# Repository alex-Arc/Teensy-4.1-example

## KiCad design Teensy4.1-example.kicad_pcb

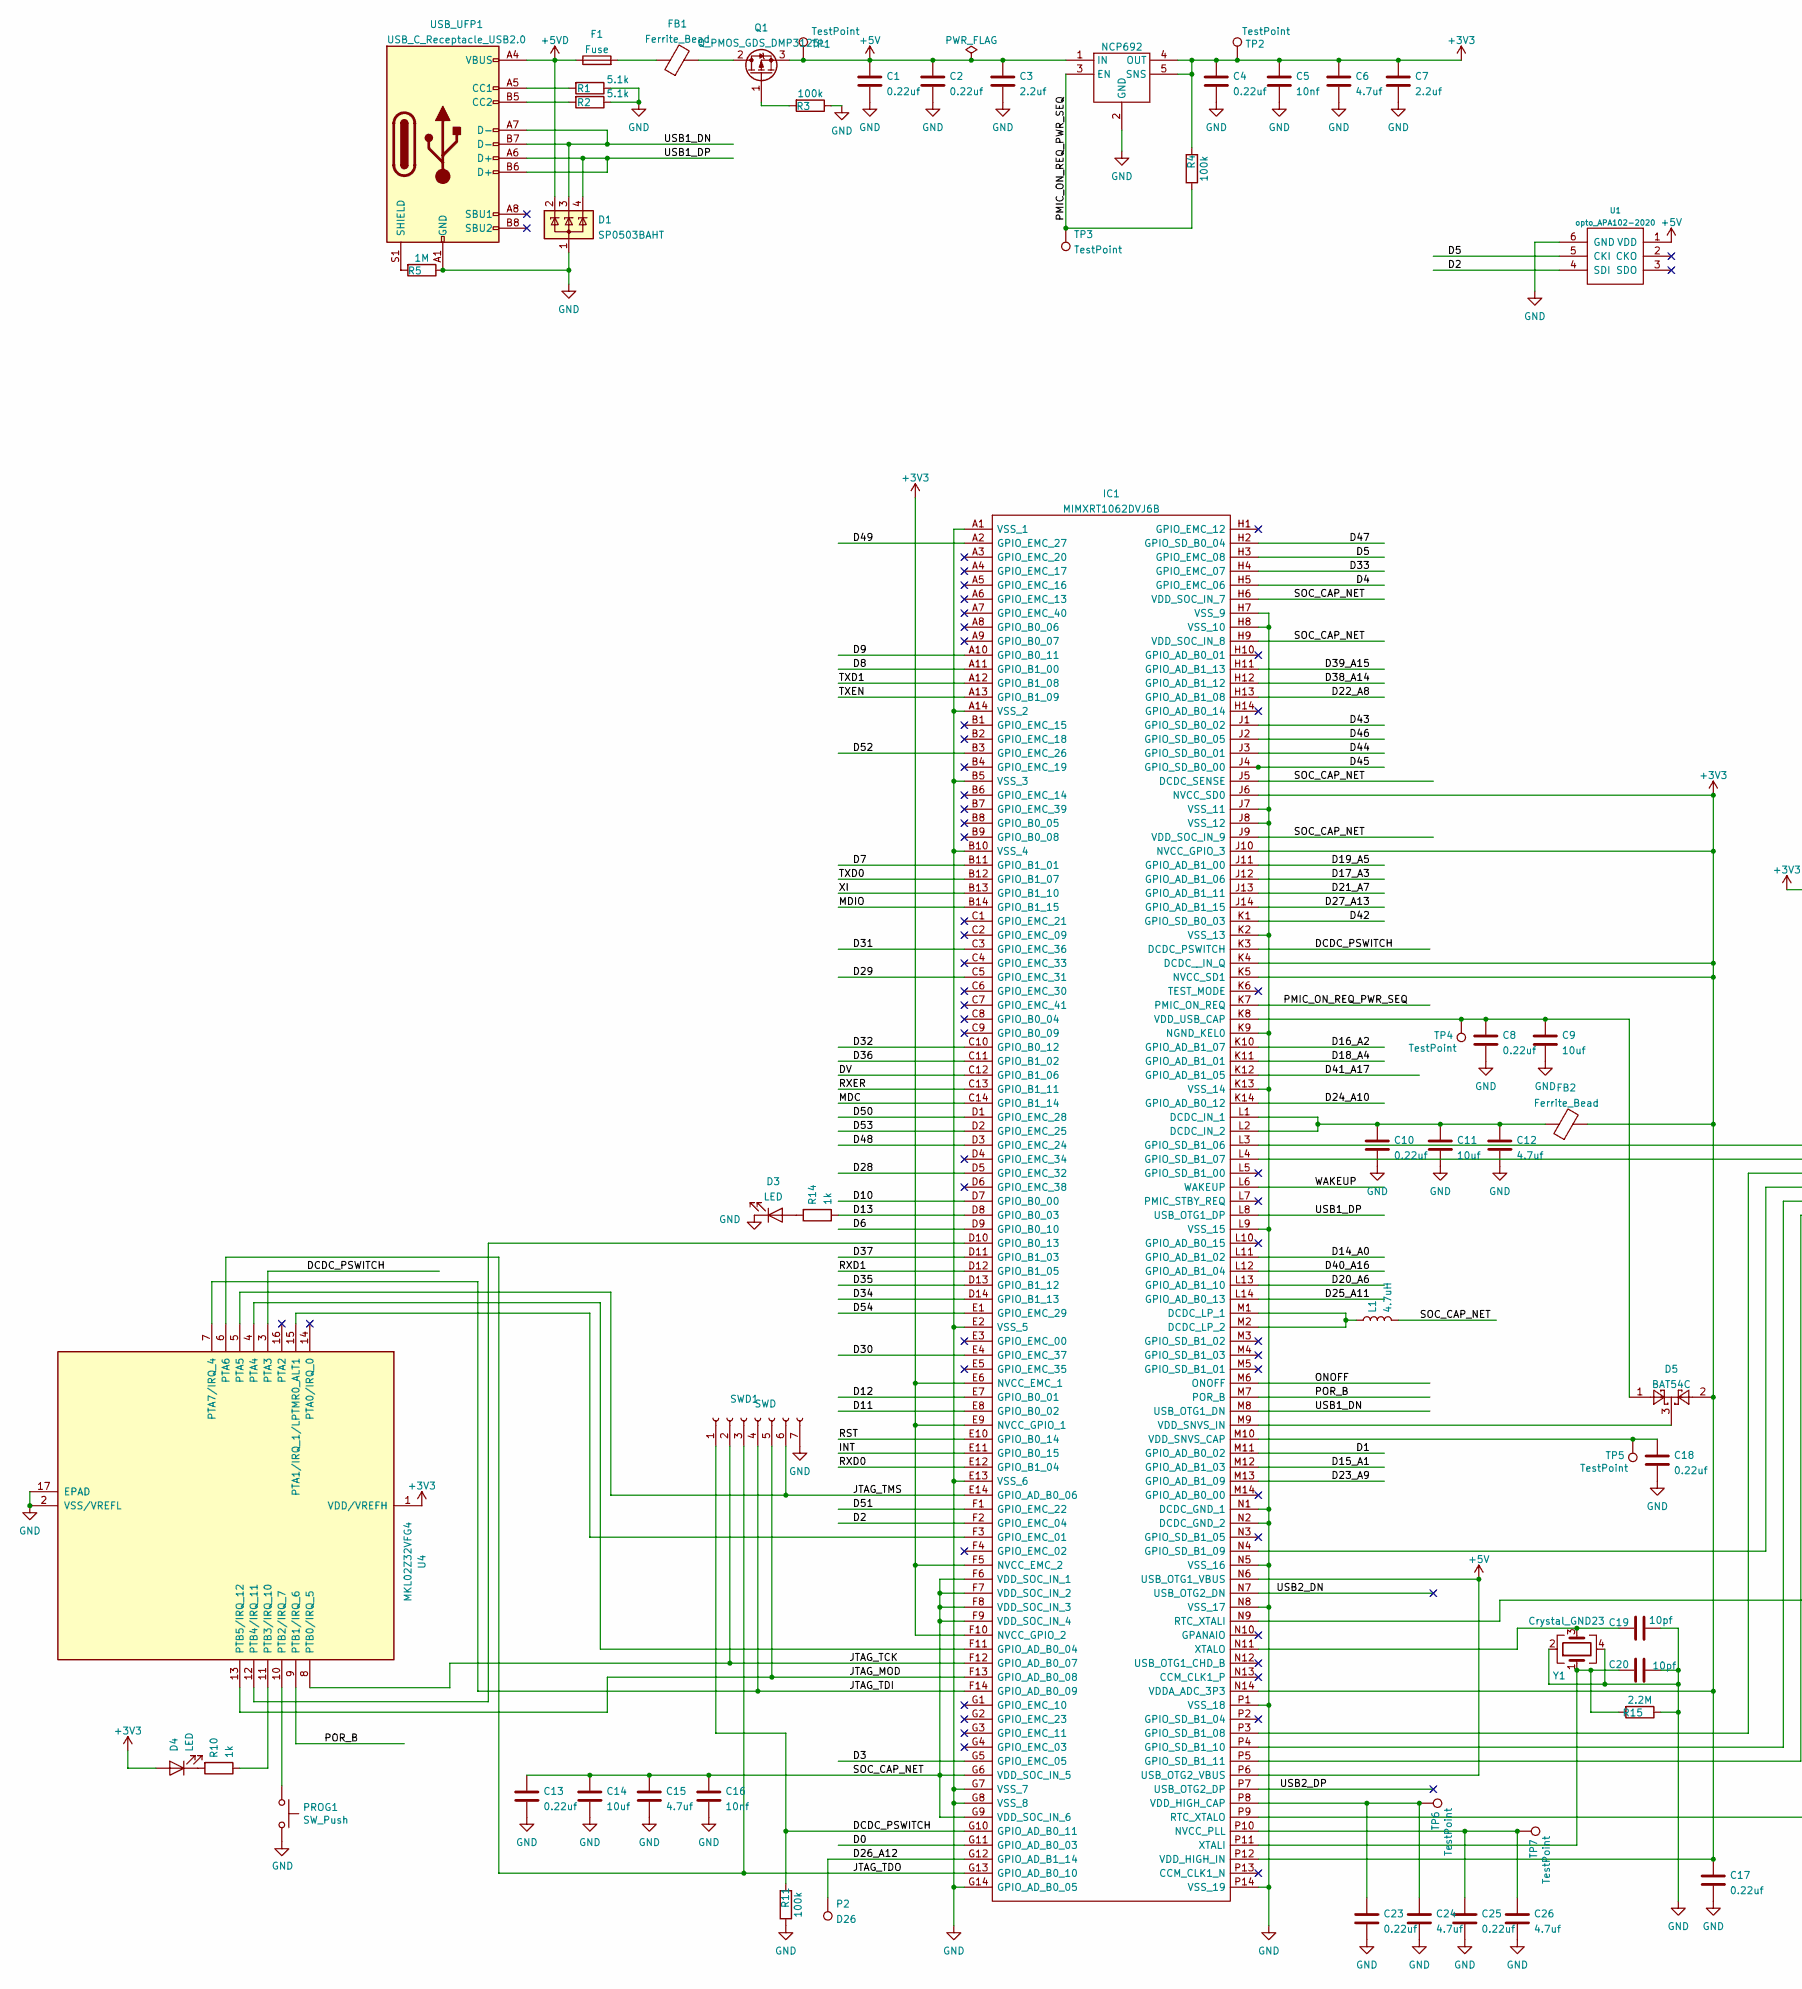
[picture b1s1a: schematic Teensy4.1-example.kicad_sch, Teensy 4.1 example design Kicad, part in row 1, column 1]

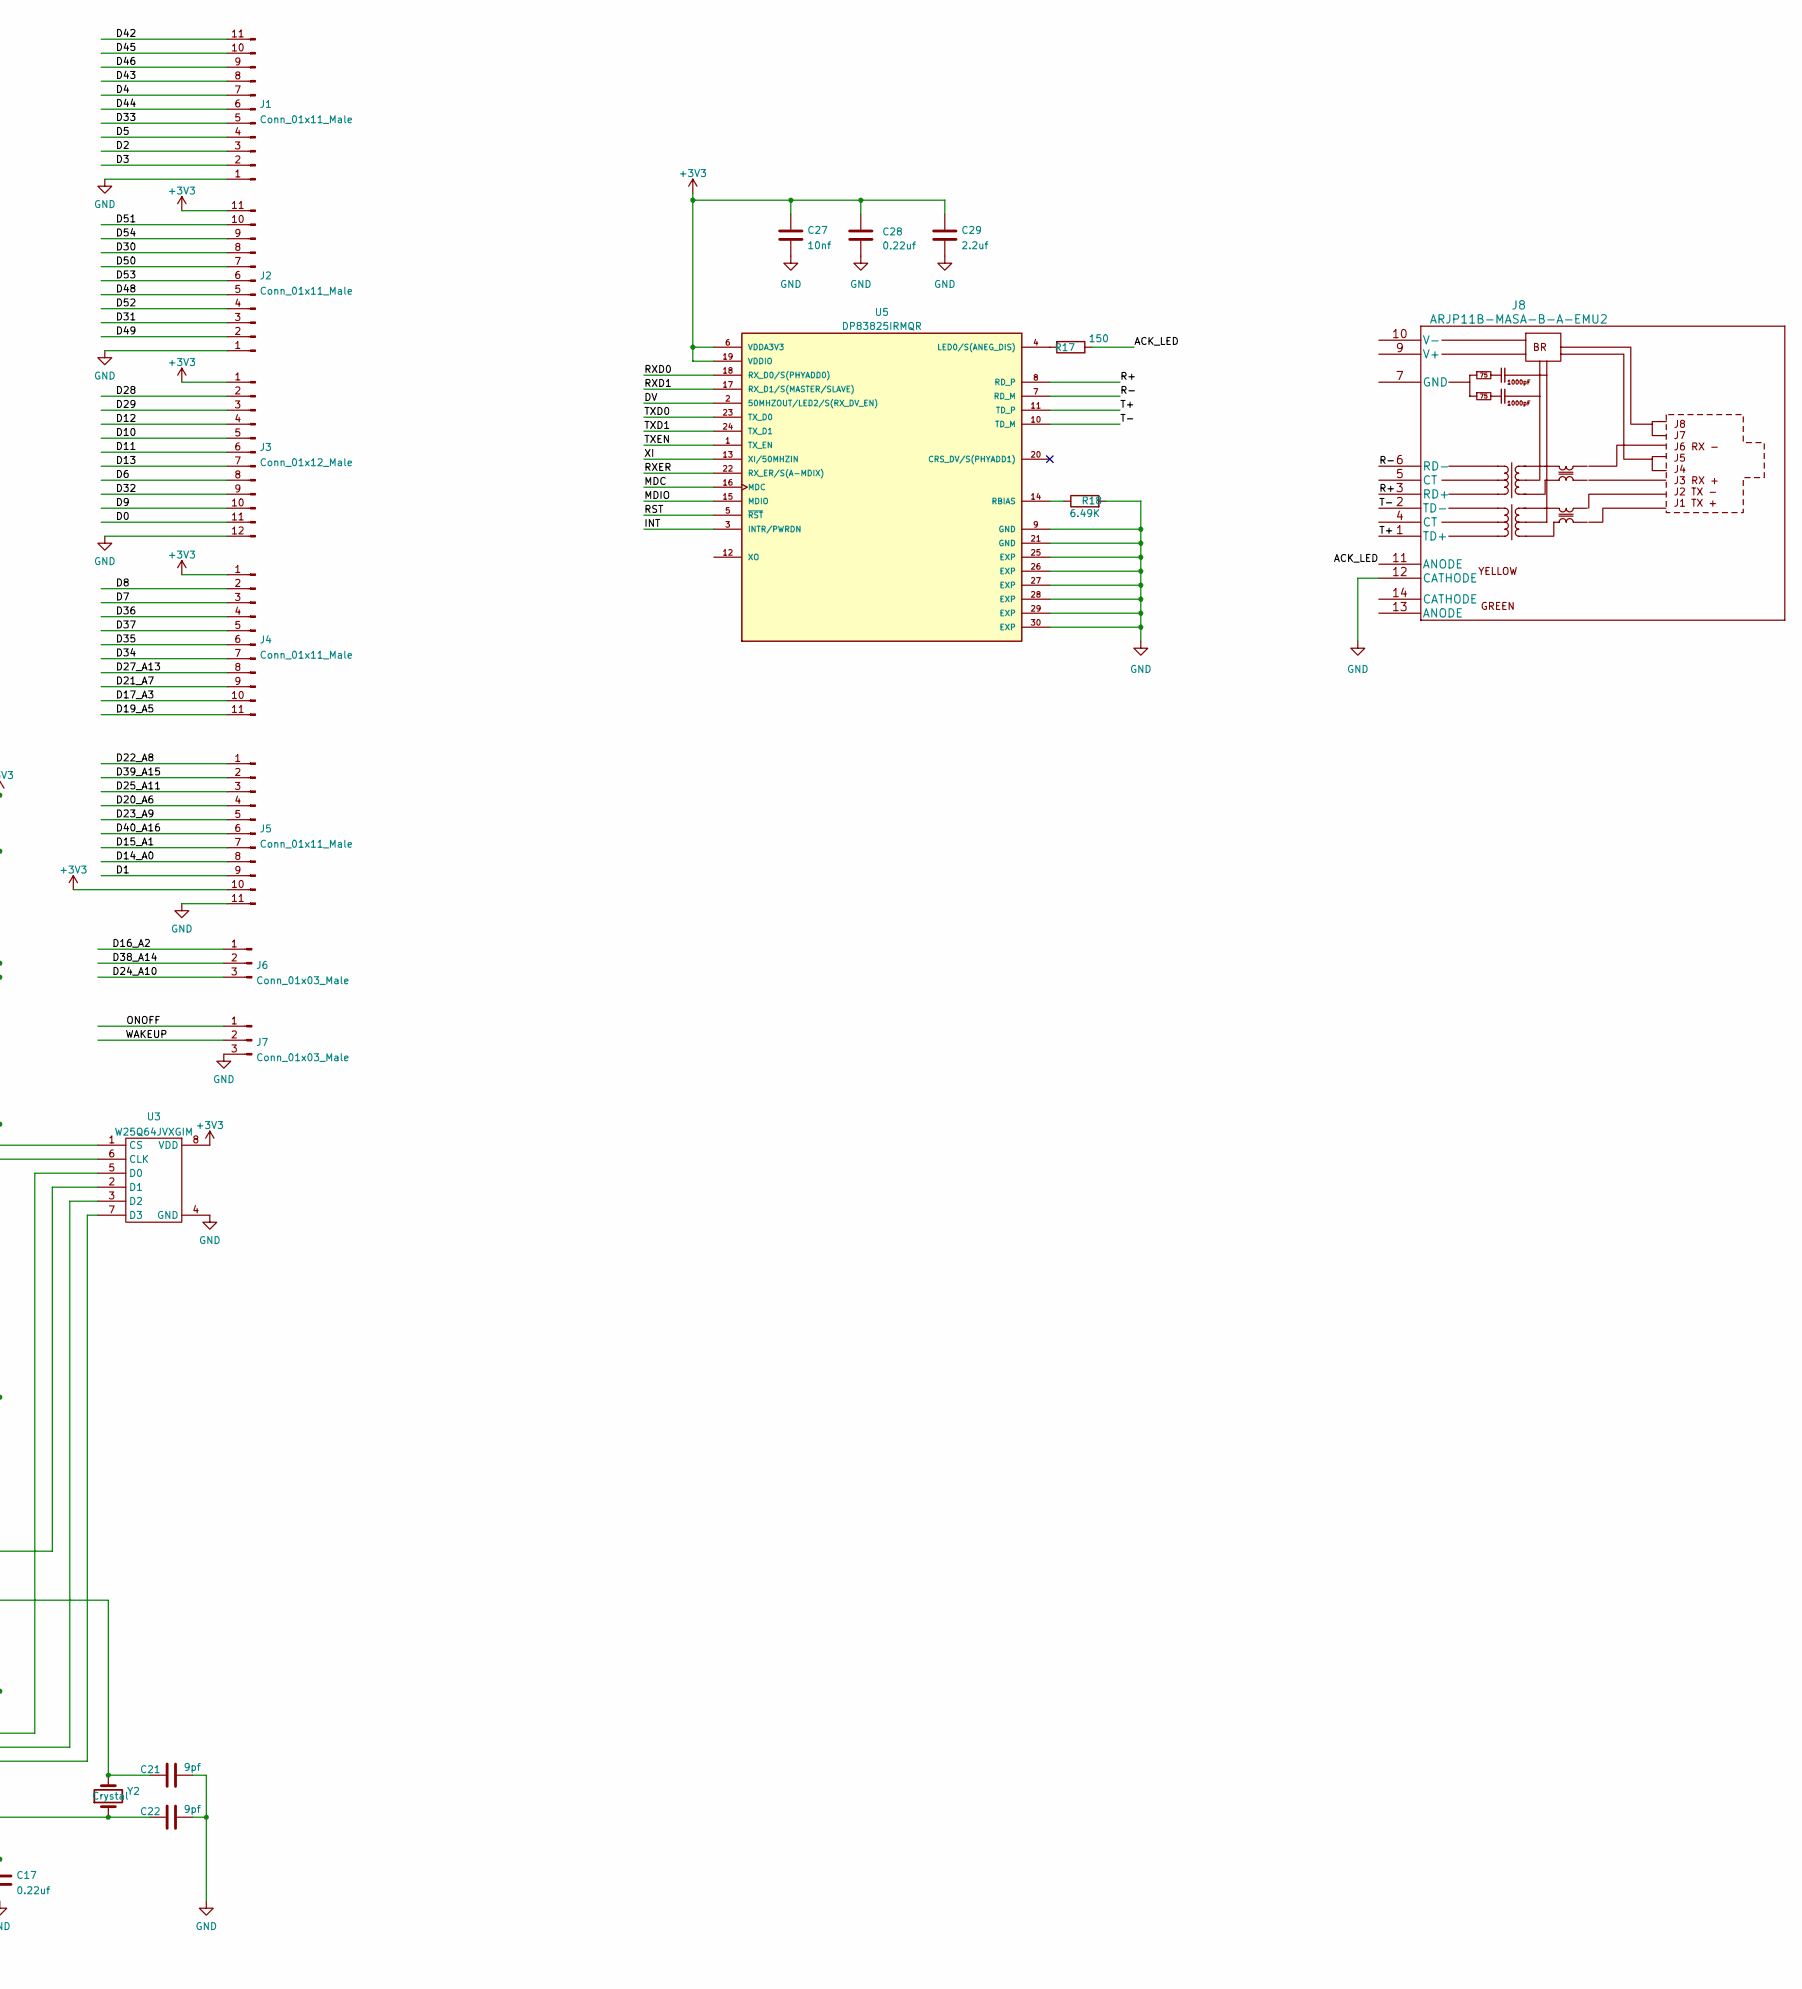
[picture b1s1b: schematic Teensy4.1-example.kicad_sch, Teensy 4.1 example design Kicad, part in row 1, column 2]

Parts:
C1, C2, C4, C8, C10, C13, C17, C18, C23, C25, C28: 0.22uf; C_0603_1608Metric; MPN CC0603KRX7R6BB224
C3, C7, C29: 2.2uf; C_0603_1608Metric; MPN CL10B225KP8NNNC
C5, C16, C27: 10nf; C_0603_1608Metric; MPN 0603B103K160CT
C6, C12, C15, C24, C26: 4.7uf; C_0603_1608Metric; MPN CL10B475KQ8NQNC
C9, C11, C14: 10uf; C_0805_2012Metric; MPN GRM21BR71A106KA73K
C19, C20: 10pf; C_0603_1608Metric; MPN CC0603KRX7R6BB224
C21, C22: 9pf; C_0603_1608Metric; MPN GRM1885C1H9R0DA01D
D1: SP0503BAHT; SOT-143
D3, D4: LED; LED_0402_1005Metric
D5: BAT54C; SOT-23
F1: Fuse; R_0805_2012Metric; MPN 0ZCK0050FF2E
FB1, FB2: Ferrite_Bead; R_0805_2012Metric; MPN FBMH2012HM121-T‎
IC1: MIMXRT1062DVJ6B; BGA196C80P14X14_1200X1200X152; Mouser Part Number 771-MIMXRT1062DVJ6B
J1, J2, J4, J5: Conn_01x11_Male; PinHeader_1x11_P2.54mm_Vertical
J3: Conn_01x12_Male; PinHeader_1x12_P2.54mm_Vertical
J6, J7: Conn_01x03_Male; PinHeader_1x03_P2.54mm_Vertical
J8: ARJP11B-MASA-B-A-EMU2
L1: 4.7uH; C_0805_2012Metric; MPN LQM21PN4R7MGRD
NCP692: OnSemi NCP692, fixed version; DFN-6-1EP_3x3mm_P0.95mm_EP1.7x2.6mm; MPN NCP692MN33T2G
P2: D26; PinHeader_1x01_P1.00mm_Vertical
PROG1: SW_Push; KMR241GLFS; MPN KMR241GLFS
Q1: Q_PMOS_GDS_DMP3125L; SOT-23
R1, R2: 5.1k; R_0603_1608Metric; MPN RC0603FR-075K1L
R3, R4, R11: 100k; R_0603_1608Metric
R5: 1M; R_0603_1608Metric
R10, R14: 1k; R_0402_1005Metric
R15: 2.2M; R_0603_1608Metric
R17: 150; R_0603_1608Metric; MPN RC0603FR-075K1L
R18: 6.49K; R_0603_1608Metric
SWD1: SWD; PinHeader_1x07_P1.27mm_Vertical
TP1, TP2, TP3, TP4, TP5, TP6, TP7: TestPoint; TestPoint_Pad_D1.0mm
U1: opto_APA102-2020; APA102-2020
U3: W25Q64JVXGIM; XSON8_4x4mm
U4: MKL02Z32VFG4; QFN-16-1EP_3x3mm_P0.5mm_EP1.8x1.8mm; MPN Custom firmware part
U5: DP83825IRMQR; XCVR_DP83825IRMQR; PARTREV A
USB_UFP1: USB_C_Receptacle_USB2.0; TYPE-C-31-M-14
Y1: Crystal_GND23; Crystal_SMD_Abracon_ABM3B-4Pin_5.0x3.2mm
Y2: Crystal; Crystal_SMD_2012-2Pin_2.0x1.2mm; MPN ABS06-32.768KHZ-9-1-T

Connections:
+3V3: C4.1, C5.1, C6.1, C7.1, C17.1, C27.1, C28.1, C29.1, D4.2 (A), D5.2, FB2.2, IC1.E6 (NVCC_EMC_1), IC1.E9 (NVCC_GPIO_1), IC1.F5 (NVCC_EMC_2), IC1.F10 (NVCC_GPIO_2), IC1.J6 (NVCC_SD0), IC1.J10 (NVCC_GPIO_3), IC1.K4 (DCDC__IN_Q), IC1.K5 (NVCC_SD1), IC1.N14 (VDDA_ADC_3P3), IC1.P12 (VDD_HIGH_IN), J2.11, J3.1, J4.1, J5.10, NCP692.4 (OUT), NCP692.5 (SNS), R4.2, TP2.1, U3.8 (VDD), U4.1 (VDD/VREFH), U5.6 (VDDA3V3), U5.19 (VDDIO)
+5V: C1.1, C2.1, C3.1, IC1.N6 (USB_OTG1_VBUS), IC1.P6 (USB_OTG2_VBUS), NCP692.1 (IN), NCP692.6 (IN), Q1.3 (S), TP1.1, U1.1 (VDD)
+5VD: D1.2 (K), F1.1, USB_UFP1.A4 (VBUS), USB_UFP1.A9 (VBUS), USB_UFP1.B4 (VBUS), USB_UFP1.B9 (VBUS); also elsewhere on the board
/ACK_LED: J8.11 (ANODE), R17.1
/D0: IC1.G11 (GPIO_AD_B0_03), J3.11
/D1: IC1.M11 (GPIO_AD_B0_02), J5.9
/D2: IC1.F2 (GPIO_EMC_04), J1.3, U1.4 (SDI)
/D3: IC1.G5 (GPIO_EMC_05), J1.2
/D4: IC1.H5 (GPIO_EMC_06), J1.7
/D5: IC1.H3 (GPIO_EMC_08), J1.4, U1.5 (CKI)
/D6: IC1.D9 (GPIO_B0_10), J3.8
/D7: IC1.B11 (GPIO_B1_01), J4.3
/D8: IC1.A11 (GPIO_B1_00), J4.2
/D9: IC1.A10 (GPIO_B0_11), J3.10
/D10: IC1.D7 (GPIO_B0_00), J3.5
/D11: IC1.E8 (GPIO_B0_02), J3.6
/D12: IC1.E7 (GPIO_B0_01), J3.4
/D13: IC1.D8 (GPIO_B0_03), J3.7, R14.1
/D14_A0: IC1.L11 (GPIO_AD_B1_02), J5.8
/D15_A1: IC1.M12 (GPIO_AD_B1_03), J5.7
/D16_A2: IC1.K10 (GPIO_AD_B1_07), J6.1
/D17_A3: IC1.J12 (GPIO_AD_B1_06), J4.10
/D18_A4: IC1.K11 (GPIO_AD_B1_01)
/D19_A5: IC1.J11 (GPIO_AD_B1_00), J4.11
/D20_A6: IC1.L13 (GPIO_AD_B1_10), J5.4
/D21_A7: IC1.J13 (GPIO_AD_B1_11), J4.9
/D22_A8: IC1.H13 (GPIO_AD_B1_08), J5.1
/D23_A9: IC1.M13 (GPIO_AD_B1_09), J5.5
/D24_A10: IC1.K14 (GPIO_AD_B0_12), J6.3
/D25_A11: IC1.L14 (GPIO_AD_B0_13), J5.3
/D26_A12: IC1.G12 (GPIO_AD_B1_14), P2.1
/D27_A13: IC1.J14 (GPIO_AD_B1_15), J4.8
/D28: IC1.D5 (GPIO_EMC_32), J3.2
/D29: IC1.C5 (GPIO_EMC_31), J3.3
/D30: IC1.E4 (GPIO_EMC_37), J2.8
/D31: IC1.C3 (GPIO_EMC_36), J2.3
/D32: IC1.C10 (GPIO_B0_12), J3.9
/D33: IC1.H4 (GPIO_EMC_07), J1.5
/D34: IC1.D14 (GPIO_B1_13), J4.7
/D35: IC1.D13 (GPIO_B1_12), J4.6
/D36: IC1.C11 (GPIO_B1_02), J4.4
/D37: IC1.D11 (GPIO_B1_03), J4.5
/D38_A14: IC1.H12 (GPIO_AD_B1_12), J6.2
/D39_A15: IC1.H11 (GPIO_AD_B1_13), J5.2
/D40_A16: IC1.L12 (GPIO_AD_B1_04), J5.6
/D41_A17: IC1.K12 (GPIO_AD_B1_05)
/D42: IC1.K1 (GPIO_SD_B0_03), J1.11
/D43: IC1.J1 (GPIO_SD_B0_02), J1.8
/D44: IC1.J3 (GPIO_SD_B0_01), J1.6
/D45: IC1.J4 (GPIO_SD_B0_00), J1.10
/D46: IC1.J2 (GPIO_SD_B0_05), J1.9
/D47: IC1.H2 (GPIO_SD_B0_04)
/D48: IC1.D3 (GPIO_EMC_24), J2.5
/D49: IC1.A2 (GPIO_EMC_27), J2.2
/D50: IC1.D1 (GPIO_EMC_28), J2.7
/D51: IC1.F1 (GPIO_EMC_22), J2.10
/D52: IC1.B3 (GPIO_EMC_26), J2.4
/D53: IC1.D2 (GPIO_EMC_25), J2.6
/D54: IC1.E1 (GPIO_EMC_29), J2.9
/DCDC_PSWITCH: IC1.G10 (GPIO_AD_B0_11), IC1.K3 (DCDC_PSWITCH), R11.2, SWD1.1, U4.3 (PTA3)
/DV: IC1.C12 (GPIO_B1_06), U5.2 (50MHZOUT/LED2/S(RX_DV_EN))
/INT: IC1.E11 (GPIO_B0_15), U5.3 (INTR/PWRDN)
/JTAG_MOD: IC1.F13 (GPIO_AD_B0_08), SWD1.5, U4.13 (PTB5/IRQ_12)
/JTAG_TCK: IC1.F12 (GPIO_AD_B0_07), SWD1.2, U4.8 (PTB0/IRQ_5)
/JTAG_TDI: IC1.F14 (GPIO_AD_B0_09), SWD1.4, U4.7 (PTA7/IRQ_4)
/JTAG_TDO: IC1.G13 (GPIO_AD_B0_10), SWD1.3, U4.6 (PTA6)
/JTAG_TMS: IC1.E14 (GPIO_AD_B0_06), SWD1.6, U4.5 (PTA5)
/MDC: IC1.C14 (GPIO_B1_14), U5.16 (MDC)
/MDIO: IC1.B14 (GPIO_B1_15), U5.15 (MDIO)
/ONOFF: IC1.M6 (ONOFF), J7.1
/PMIC_ON_REQ_PWR_SEQ: IC1.K7 (PMIC_ON_REQ), NCP692.3 (EN), R4.1, TP3.1
/POR_B: IC1.M7 (POR_B), U4.9 (PTB1/IRQ_6)
/R+: J8.3 (RD+), U5.8 (RD_P)
/R-: J8.6 (RD-), U5.7 (RD_M)
/RST: IC1.E10 (GPIO_B0_14), U5.5 (~RST)
/RXD0: IC1.E12 (GPIO_B1_04), U5.18 (RX_D0/S(PHYADD0))
/RXD1: IC1.D12 (GPIO_B1_05), U5.17 (RX_D1/S(MASTER/SLAVE))
/RXER: IC1.C13 (GPIO_B1_11), U5.22 (RX_ER/S(A-MDIX))
/SOC_CAP_NET: C13.1, C14.1, C15.1, C16.1, IC1.F6 (VDD_SOC_IN_1), IC1.F7 (VDD_SOC_IN_2), IC1.F8 (VDD_SOC_IN_3), IC1.F9 (VDD_SOC_IN_4), IC1.G6 (VDD_SOC_IN_5), IC1.G9 (VDD_SOC_IN_6), IC1.H6 (VDD_SOC_IN_7), IC1.H9 (VDD_SOC_IN_8), IC1.J5 (DCDC_SENSE), IC1.J9 (VDD_SOC_IN_9), L1.2
/T+: J8.1 (TD+), U5.11 (TD_P)
/T-: J8.2 (TD-), U5.10 (TD_M)
/TXD0: IC1.B12 (GPIO_B1_07), U5.23 (TX_D0)
/TXD1: IC1.A12 (GPIO_B1_08), U5.24 (TX_D1)
/TXEN: IC1.A13 (GPIO_B1_09), U5.1 (TX_EN)
/USB1_DN: D1.3 (K), IC1.M8 (USB_OTG1_DN), USB_UFP1.A7 (D-), USB_UFP1.B7 (D-)
/USB1_DP: D1.4 (K), IC1.L8 (USB_OTG1_DP), USB_UFP1.A6 (D+), USB_UFP1.B6 (D+)
/USB2_DN: IC1.N7 (USB_OTG2_DN)
/USB2_DP: IC1.P7 (USB_OTG2_DP)
/WAKEUP: IC1.L6 (WAKEUP), J7.2
/XI: IC1.B13 (GPIO_B1_10), U5.13 (XI/50MHZIN)
GND: C1.2, C2.2, C3.2, C4.2, C5.2, C6.2, C7.2, C8.2, C9.2, C10.2, C11.2, C12.2, C13.2, C14.2, C15.2, C16.2, C17.2, C18.2, C19.2, C20.2, C21.2, C22.2, C23.2, C24.2, C25.2, C26.2, C27.2, C28.2, C29.2, D1.1 (A), D3.1 (K), IC1.A1 (VSS_1), IC1.A14 (VSS_2), IC1.B5 (VSS_3), IC1.B10 (VSS_4), IC1.E2 (VSS_5), IC1.E13 (VSS_6), IC1.G7 (VSS_7), IC1.G8 (VSS_8), IC1.G14 (GPIO_AD_B0_05), IC1.H7 (VSS_9), IC1.H8 (VSS_10), IC1.J7 (VSS_11), IC1.J8 (VSS_12), IC1.K2 (VSS_13), IC1.K9 (NGND_KEL0), IC1.K13 (VSS_14), IC1.L9 (VSS_15), IC1.N1 (DCDC_GND_1), IC1.N2 (DCDC_GND_2), IC1.N5 (VSS_16), IC1.N8 (VSS_17), IC1.P1 (VSS_18), IC1.P14 (VSS_19), J1.1, J2.1, J3.12, J5.11, J7.3, J8.12 (CATHODE), NCP692.2 (GND), NCP692.7 (GND), PROG1.2, R1.1, R2.1, R3.1, R5.1, R11.1, R15.1, R18.2, SWD1.7, U1.6 (GND), U3.4 (GND), U4.2 (VSS/VREFL), U4.17 (EPAD), U5.9 (GND), U5.21 (GND), U5.25 (EXP), U5.26 (EXP), U5.27 (EXP), U5.28 (EXP), U5.29 (EXP), U5.30 (EXP), USB_UFP1.A1 (GND), USB_UFP1.A12 (GND), USB_UFP1.B1 (GND), USB_UFP1.B12 (GND), Y1.2, Y1.4; also elsewhere on the board
unnamed: D3.2 (A), R14.2
unnamed: D4.1 (K), R10.2
unnamed: F1.2, FB1.1
unnamed: C10.1, C11.1, C12.1, FB2.1, IC1.L1 (DCDC_IN_1), IC1.L2 (DCDC_IN_2)
unnamed: IC1.M1 (DCDC_LP_1), IC1.M2 (DCDC_LP_2), L1.1
unnamed: IC1.F11 (GPIO_AD_B0_04), U4.4 (PTA4)
unnamed: IC1.D10 (GPIO_B0_13), U4.12 (PTB4/IRQ_11)
unnamed: IC1.F3 (GPIO_EMC_01), U4.15 (PTA1/IRQ_1/LPTMR0_ALT1)
unnamed: IC1.L3 (GPIO_SD_B1_06), U3.1 (CS)
unnamed: IC1.L4 (GPIO_SD_B1_07), U3.6 (CLK)
unnamed: IC1.P3 (GPIO_SD_B1_08), U3.5 (D0)
unnamed: IC1.N4 (GPIO_SD_B1_09), U3.2 (D1)
unnamed: IC1.P4 (GPIO_SD_B1_10), U3.3 (D2)
unnamed: IC1.P5 (GPIO_SD_B1_11), U3.7 (D3)
unnamed: C25.1, C26.1, IC1.P10 (NVCC_PLL), TP7.1
unnamed: C21.1, IC1.N9 (RTC_XTALI), Y2.2
unnamed: C22.1, IC1.P9 (RTC_XTALO), Y2.1
unnamed: C23.1, C24.1, IC1.P8 (VDD_HIGH_CAP), TP6.1
unnamed: C18.1, IC1.M10 (VDD_SNVS_CAP), TP5.1
unnamed: D5.3, IC1.M9 (VDD_SNVS_IN)
unnamed: C8.1, C9.1, D5.1, IC1.K8 (VDD_USB_CAP), TP4.1
unnamed: C20.1, IC1.P11 (XTALI), R15.2, Y1.1
unnamed: C19.1, IC1.N11 (XTALO), Y1.3
unnamed: FB1.2, Q1.2 (D)
unnamed: Q1.1 (G), R3.2
unnamed: PROG1.1, U4.10 (PTB2/IRQ_7)
unnamed: R10.1, U4.11 (PTB3/IRQ_10)
unnamed: R17.2, U5.4 (LED0/S(ANEG_DIS))
unnamed: R18.1, U5.14 (RBIAS)
unnamed: R1.2, USB_UFP1.A5 (CC1)
unnamed: R2.2, USB_UFP1.B5 (CC2)
unnamed: R5.2, USB_UFP1.S1 (SHIELD)

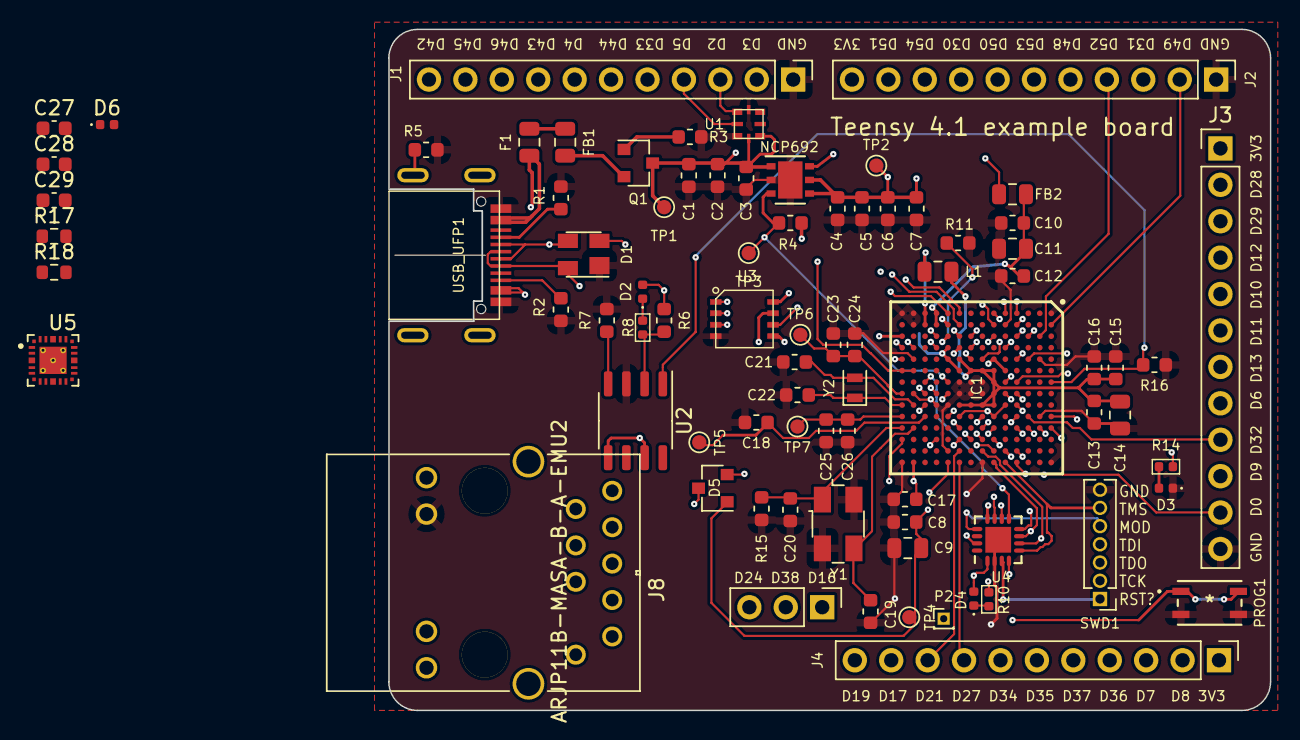
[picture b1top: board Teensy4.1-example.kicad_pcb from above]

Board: 4 copper layers, 61.5 x 47.5 mm, 81 parts (0 on the bottom side), 112 nets.

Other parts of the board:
D2, D6: LED; LED_0402_1005Metric
R6, R7: 16k; R_0603_1608Metric
R8: 1k; R_0402_1005Metric
R16: 100k; R_0603_1608Metric
U2: MAX1562; SO-8_3.9x4.9mm_P1.27mm

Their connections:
+5VD: D2.2 (A), R6.1, U2.5 (IN), U2.7 (IN); also elsewhere on the board
+5VL: U2.6 (OUT), U2.8 (OUT)
GND: D6.1 (K), R7.1, R16.1, U2.3 (GND); also elsewhere on the board
unnamed: D2.1 (K), R8.1
unnamed: R16.2, U2.1 (ON)
unnamed: R6.2, R8.2, U2.2 (Fault)
unnamed: R7.2, U2.4 (ISET)

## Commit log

2023-04-17 add phy chip to schematic
2023-04-17 add ARJP11B magjack

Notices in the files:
parts and their libraries:
Copyright 2016 Accelerated Designs. All rights reserved.
